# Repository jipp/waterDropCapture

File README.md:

# waterDropCapture

## The following features are implemented
* the sensor will trigger the DSLR assuming a hight of 0,5m

## Installation
Put the waterDropCapture folder into the local Arduino folder.

## Additional files
EAGLE files included:
* Circuit diagram
* Board layout

OpenSCAD files included:
* tube to hold the sensor and be plugged over a bottle

## Info
This was developed 1st for a Nikon, but as a 2.5mm Jack is used to connect the camera any camera adapter should work.
The tube should fit on many water bottles.

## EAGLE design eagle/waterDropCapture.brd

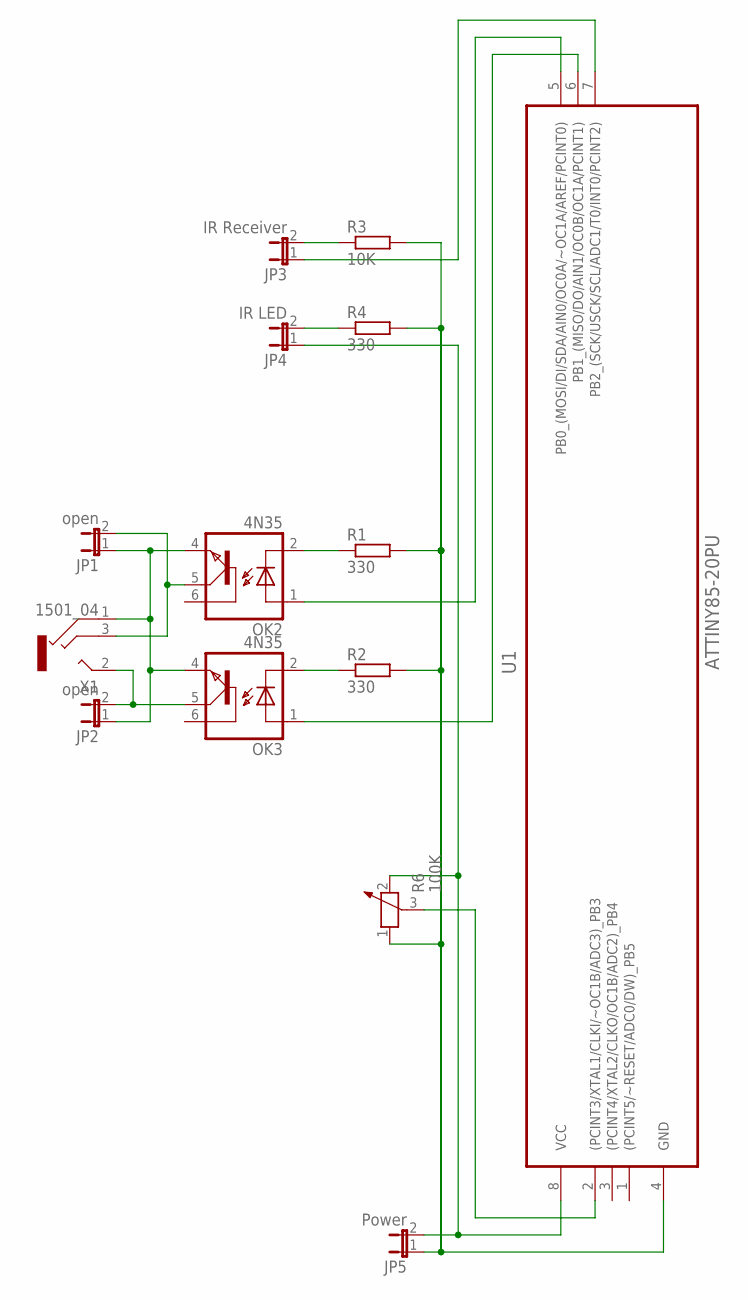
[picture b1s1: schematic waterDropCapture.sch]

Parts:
JP1, JP2: open; JP1
JP3: IR Receiver; JP1
JP4: IR LED; JP1
JP5: Power; JP1
OK2, OK3: 4N35; DIL06
R1, R2, R4: 330; 0207/10
R3: 10K; 0207/10
R6: 100K; PT-10
U1: ATTINY85-20PU; DIP254P762X533-8
X1: 1501_04; 1501_05

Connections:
unnamed: OK2.2 (C), R1.1
unnamed: OK3.2 (C), R2.1
unnamed: JP1.1, JP2.1, OK2.4 (EMI), OK3.4 (EMI), X1.1
unnamed: OK2.1 (A), U1.5 (PB0_(MOSI/DI/SDA/AIN0/OC0A/~OC1A/AREF/P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)
unnamed: JP2.2, OK3.5 (COL), X1.2
unnamed: JP5.1, R1.2, R2.2, R3.2, R4.2, R6.1, U1.4 (GND)
unnamed: OK3.1 (A), U1.6 (PB1_(MISO/DO/AIN1/OC0B/OC1A/PCINT1))
unnamed: JP4.2, R4.1
unnamed: JP1.2, OK2.5 (COL), X1.3
unnamed: JP4.1, JP5.2, R6.2, U1.8 (VCC)
unnamed: JP3.2, R3.1
unnamed: JP3.1, U1.7 (PB2_(SCK/USCK/SCL/ADC1/T0/INT0/PCINT2))
unnamed: R6.3, U1.2 ((PCINT3/XTAL1/CLKI/~OC1B/ADC3)_PB3)

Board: 2 copper layers, 14 parts (0 on the bottom side), 13 nets, no tracks yet.

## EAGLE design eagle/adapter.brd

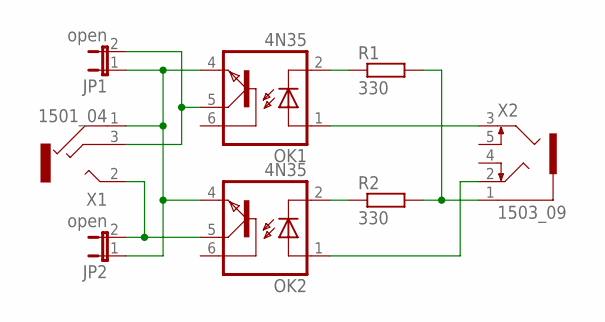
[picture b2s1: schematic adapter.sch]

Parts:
JP1, JP2: open; JP1
OK1, OK2: 4N35; DIL06
R1, R2: 330; 0207/10
X1: 1501_04; 1501_05
X2: 1503_09

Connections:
unnamed: JP1.1, JP2.1, OK1.4 (EMI), OK2.4 (EMI), X1.1
unnamed: OK1.2 (C), R1.1
unnamed: OK2.2 (C), R2.1
unnamed: R1.2, R2.2, X2.1
unnamed: JP1.2, OK1.5 (COL), X1.3
unnamed: JP2.2, OK2.5 (COL), X1.2
unnamed: OK2.1 (A), X2.2
unnamed: OK1.1 (A), X2.3

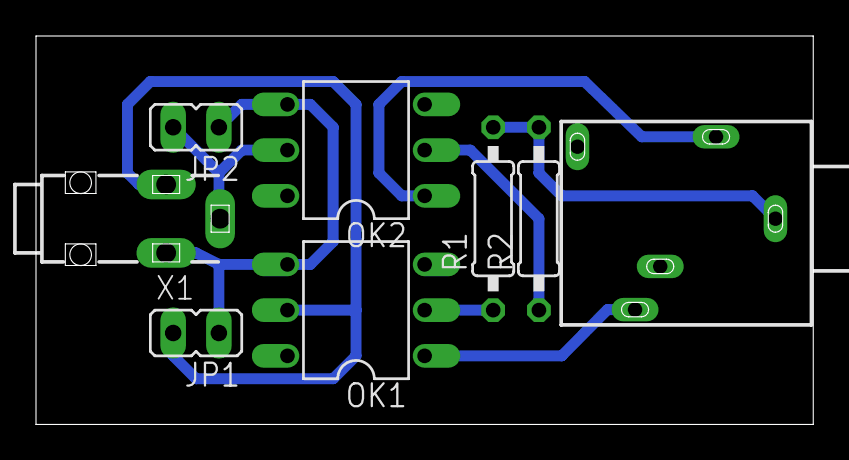
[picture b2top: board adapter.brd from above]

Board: 2 copper layers, 43.2 x 21.6 mm, 8 parts (0 on the bottom side), 8 nets.

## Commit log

2015-04-21 added Source Code
2015-04-21 for 3D printer
2015-04-21 removed .gitignore
2015-04-21 added circuit drawing and board layout
2015-05-01 remove include for Arduino.h
2017-11-12 added license
